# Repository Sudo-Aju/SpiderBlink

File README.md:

<div align="center">

# 

A Tiny LED Blinker in Shape of a Spiderweb

### _Blinks every time it gets the tingle._

</p>
</div>

# Overview

**SpiderBlink** is a 555 LED chaser board that blinks 10 LEDs in a variable speed sequence using a **NE555P** timer IC and a **CD4017** decade counter. I built this as a beginner PCB project to learn schematic design, PCB routing, and hands-on soldering.

---

# Gallery

<div align="center">

</div>

---

# Zine

<div align="center">

</div>

---

# Motivation

I wanted to dvelve deeper into embedded electronics, so thought this might be the chance for me to understand more about ICs, Timers and Oscillators

---

## Bill of Materials

|Reference|Description                     |Manufacturer     |MPN               |Quantity|Supplier         |Unit Price (USD)|Extended Price (USD)|Product Link                                                                     |
|---------|--------------------------------|-----------------|------------------|--------|-----------------|----------------|--------------------|---------------------------------------------------------------------------------|
|C1       |0.01 µF Ceramic Capacitor       |Murata           |GRM188R71H103KA01D|1       |Murata           |0.10            |0.10                |https://www.murata.com/en-global/products/productdetail?partno=GRM188R71H103KA01D|
|C2       |1 µF Ceramic Capacitor          |Murata           |GRM188R60J105KA01D|1       |Murata           |0.15            |0.15                |https://www.murata.com/en-global/products/productdetail?partno=GRM188R60J105KA01D|
|D1-D10   |5 mm Red LED                    |Kingbright       |WP7113ID          |10      |Kingbright       |0.18            |1.80                |https://www.kingbrightusa.com/product.asp?catalog_name=LED&product_id=WP7113ID   |
|R1       |1 kΩ 1/4W Through-Hole Resistor |Yageo            |CFR-25JB-52-1K    |1       |Yageo            |0.02            |0.02                |https://www.yageo.com/en/Product/Search?partNumber=CFR-25JB-52-1K                |
|R2       |470 Ω 1/4W Through-Hole Resistor|Yageo            |CFR-25JB-52-470R  |1       |Yageo            |0.02            |0.02                |https://www.yageo.com/en/Product/Search?partNumber=CFR-25JB-52-470R              |
|RV1      |50 kΩ Trimmer Potentiometer     |Bourns           |3362P-1-503LF     |1       |Bourns           |1.25            |1.25                |https://www.bourns.com/products/trimpot-trimming-potentiometers/product/3362     |
|U1       |NE555P Timer IC                 |Texas Instruments|NE555P            |1       |Texas Instruments|0.60            |0.60                |https://www.ti.com/product/NE555                                                 |
|U2       |CD4017B Decade Counter          |Texas Instruments|CD4017B           |1       |Texas Instruments|0.75            |0.75                |https://www.ti.com/product/CD4017B                                               |

---

# Features

- Heartbeat: An NE555 timer generates the clock signal.
- Speed Control: A 50kΩ potentiometer adjusts the LED flashing speed.
- Sequencer: A CD4017 decade counter cycles the signal through 10 steps.
- Rotating Effect: 10 LEDs arranged in a circular pattern for a rotating effect.

---

# PCB Design

The PCB was designed with the reference of a piderweb, more specifically Spiderman

## PCB

## Schematic

---

# Current Status

- [X] Initial Concept
- [X] Schematic Design
- [X] PCB Design
- [X] Hardware Validation
- [ ] Functional Testing
- [ ] Community Evaluation 

---

# Repository Structure

```bash
SpiderBlink/
├── PCB/
├── BOM.csv
├── Gallery/
└── README.md
```

---

# Assemble Guide

## 1. Order the PCB

Navigate to:

```bash
./PCB/Gerber.zip
```

Upload the Gerber files to your preferred PCB manufacturer.

---

## 2. Order Components

All required components can be found in:

```bash
./PCB/BOM.csv
```

---

## 3. Solder the Components

Recommended assembly should follow a low-profile to high-profile sequence to simplify alignment and reduce rework.

Suggested order:

1. 1/4W Resistors (R1, R2)
2. Ceramic Capacitors (C1, C2)
3. NE555P
4. 5mm LEDs (D1–D10)

---

## 4. Inspect the Board

Before powering:
- Check for shorts
- Verify connections
- Inspect power rails

---

# Contributing

Contributions, suggestions, and feedback are welcome.

If you'd like to improve SpiderBlink:

```bash
git clone https://github.com/Sudo-Aju/SpiderBlink.git
cd SpiderBlink
```

1. Create a feature branch
2. Make your changes
3. Commit your work
4. Open a pull request

---

# Creator

### Azmeer Pirani

Built with ❤️ for:
- Embedded Systems
- PCB Design
- Open Source Hardware
- Tiny Things

---

# License

This project is licensed under the MIT License.

---

<div align="center">

## SPIDERBLINK

### _Blinks every time it gets the tingle._

</div>

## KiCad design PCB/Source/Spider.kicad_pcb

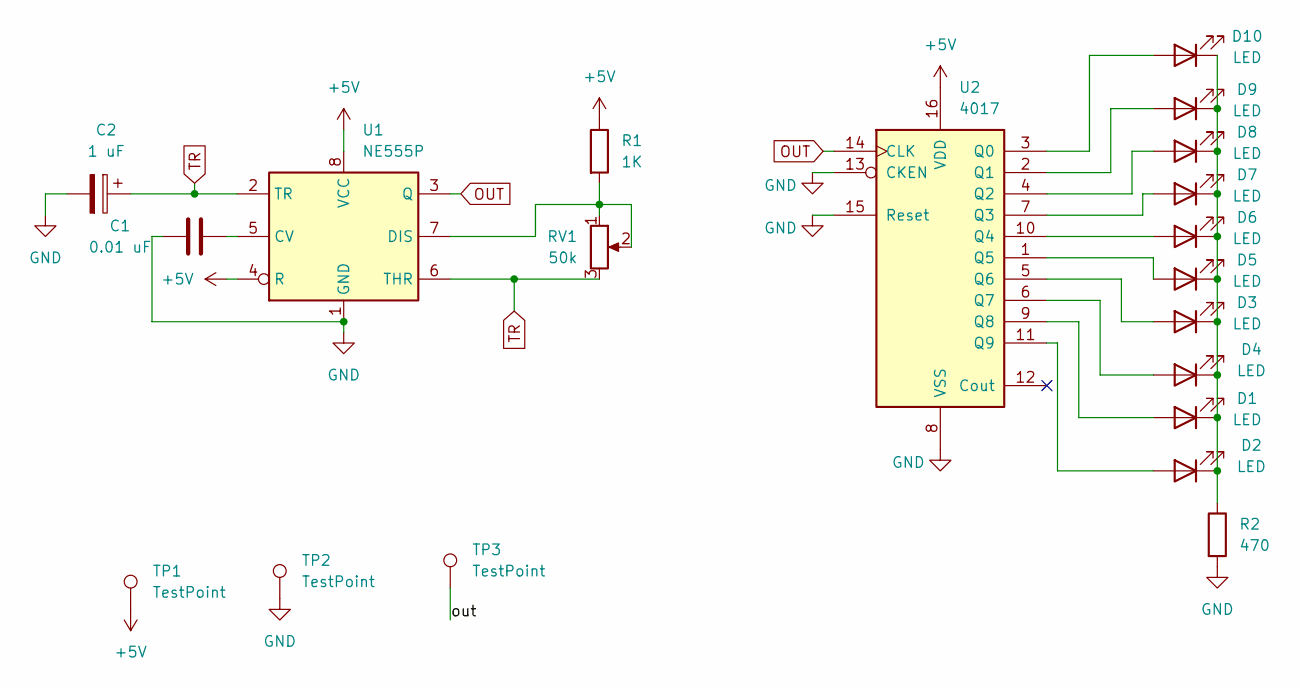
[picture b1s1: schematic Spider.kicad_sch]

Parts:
C1: 0.01 uF; CP_Radial_D5.0mm_P2.00mm
C2: 1 uF; CP_Radial_D5.0mm_P2.00mm
D1, D2, D3, D4, D5, D6, D7, D8, D9, D10: LED; LED_D3.0mm
R1: 1K; R_Axial_DIN0207_L6.3mm_D2.5mm_P7.62mm_Horizontal
R2: 470; R_Axial_DIN0207_L6.3mm_D2.5mm_P7.62mm_Horizontal
RV1: 50k; TRIM_3362P-1-102
TP1, TP2, TP3: TestPoint; PinSocket_1x01_P2.54mm_Vertical
U1: NE555P; DIP-8_W7.62mm
U2: 4017; N16

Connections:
+5V: R1.1, TP1.1, U1.4 (R), U1.8 (VCC), U2.16 (VDD)
/out: TP3.1
GND: C1.1, C2.2, R2.2, TP2.1, U1.1 (GND), U2.8 (VSS), U2.13 (CKEN), U2.15 (Reset)
unnamed: D1.2 (A), U2.9 (Q8)
unnamed: D1.1 (K), D2.1 (K), D3.1 (K), D4.1 (K), D5.1 (K), D6.1 (K), D7.1 (K), D8.1 (K), D9.1 (K), D10.1 (K), R2.1
unnamed: D2.2 (A), U2.11 (Q9)
unnamed: D3.2 (A), U2.5 (Q6)
unnamed: D4.2 (A), U2.6 (Q7)
unnamed: D5.2 (A), U2.1 (Q5)
unnamed: D6.2 (A), U2.10 (Q4)
unnamed: D7.2 (A), U2.7 (Q3)
unnamed: D8.2 (A), U2.4 (Q2)
unnamed: D9.2 (A), U2.2 (Q1)
unnamed: D10.2 (A), U2.3 (Q0)
unnamed: C1.2, U1.5 (CV)
unnamed: R1.2, RV1.1, RV1.2, U1.7 (DIS)
OUT: U1.3 (Q), U2.14 (CLK)
TR: C2.1, RV1.3, U1.2 (TR), U1.6 (THR)

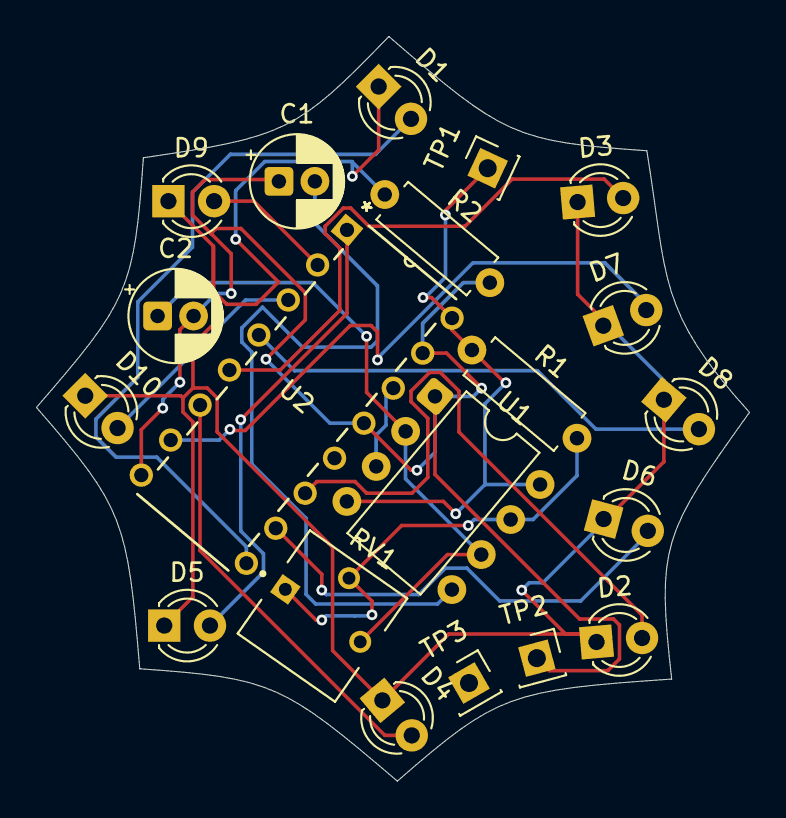
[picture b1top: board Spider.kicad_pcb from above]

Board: 2 copper layers, 39.6 x 41.4 mm, 20 parts (0 on the bottom side), 17 nets.

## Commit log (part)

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2026-06-23 made lot of updates, changed images, added few sources, and added pcb 3d model
2026-06-23 Updated images, BOM, and project file
2026-06-23 added zine and logo
